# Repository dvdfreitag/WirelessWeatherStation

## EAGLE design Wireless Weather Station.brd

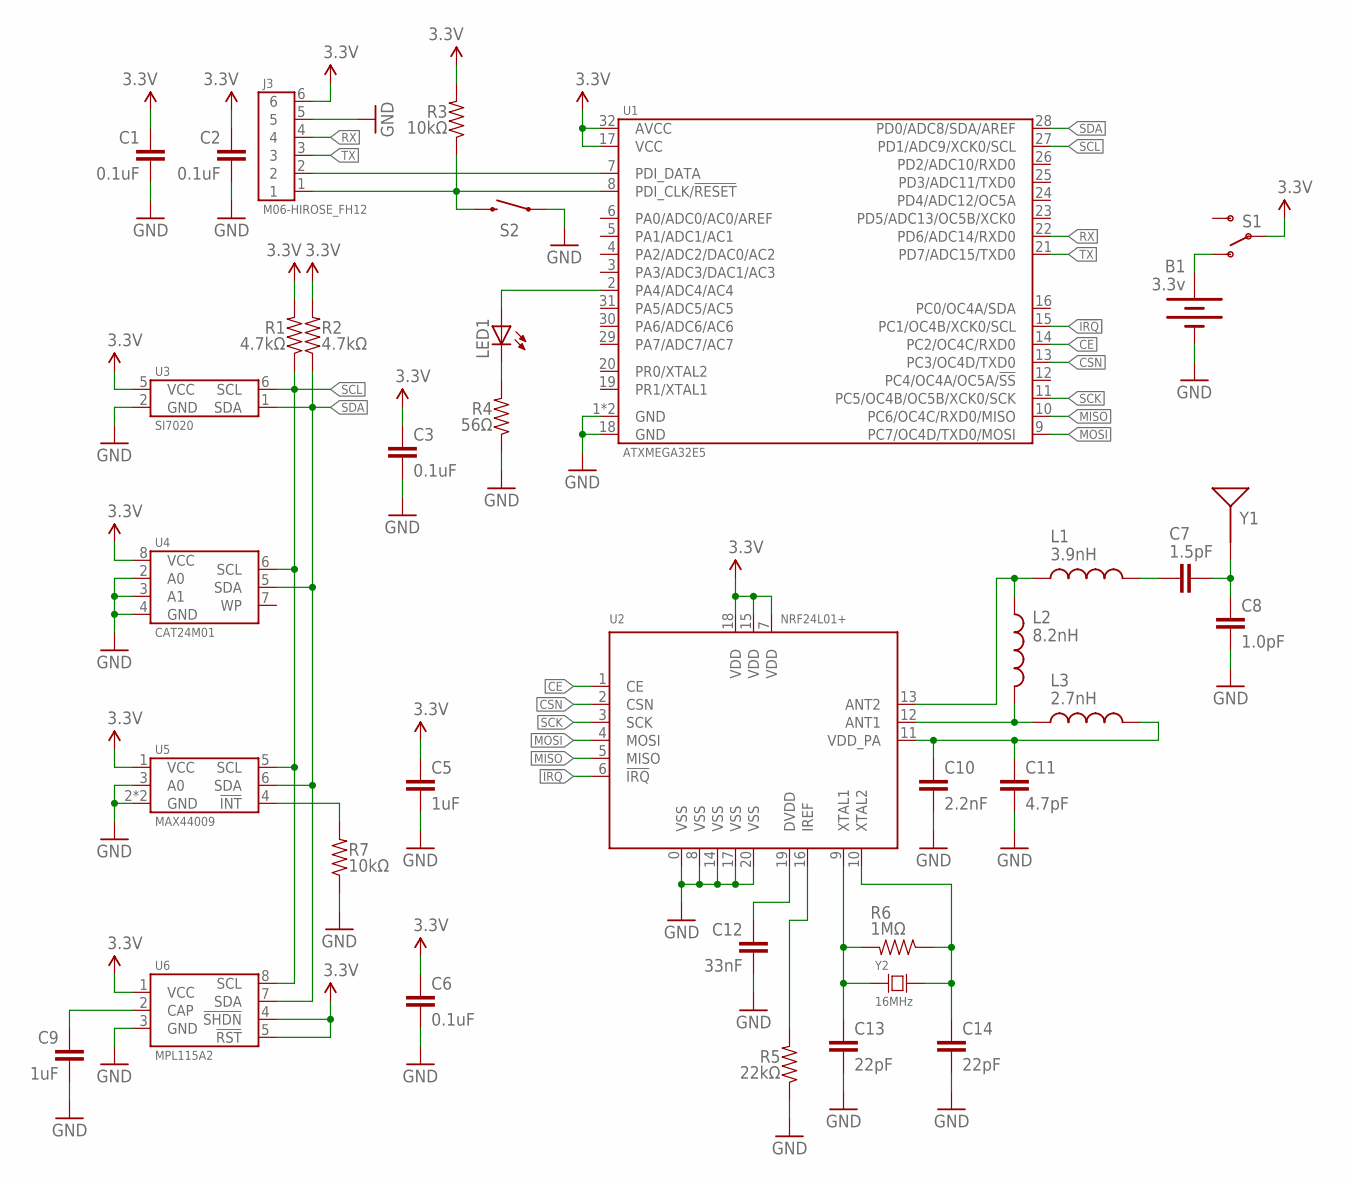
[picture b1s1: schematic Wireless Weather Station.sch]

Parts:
B1: 3.3v; BATTCON_20MM_SEWABLE
C1, C2, C3, C6: 0.1uF; 0402-CAP
C5, C9: 1uF; 0402-CAP
C7: 1.5pF; 0402-CAP
C8: 1.0pF; 0402-CAP
C10: 2.2nF; 0402-CAP
C11: 4.7pF; 0402-CAP
C12: 33nF; 0402-CAP
C13, C14: 22pF; 0402-CAP
J3: M06-HIROSE_FH12; FH12-6S-1SH(55)
L1: 3.9nH; C0402
L2: 8.2nH; C0402
L3: 2.7nH; C0402
LED1: LED0603; LED-0603
R1, R2: 4.7kΩ; 0402-RES
R3, R7: 10kΩ; 0402-RES
R4: 56Ω; 0402-RES
R5: 22kΩ; 0402-RES
R6: 1MΩ; 0402-RES
S1: SWITCH-SPDT-SMD-A; SWITCH-SPST-SMD-A
S2: SWITCH-MOMENTARY-2-SMD-1101NE; TACTILE-SWITCH-1101NE
U1: ATXMEGA32E5; QFN-32
U2: NRF24L01+; QFN-20
U3: SI7020
U4: CAT24M01; SO-8
U5: MAX44009
U6: MPL115A2; MPL115A1
Y1: ANTENNA2SMD5; ANTENNA-CHIP5
Y2: 16MHz; FA-238

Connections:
3.3V: C1.1, C2.1, C3.1, C5.1, C6.1, J3.6, R1.2, R2.2, R3.2, S1.2, U1.17 (VCC), U1.32 (AVCC), U2.7 (VDD), U2.15 (VDD), U2.18 (VDD), U3.5 (VCC), U4.8 (VCC), U5.1 (VCC), U6.1 (VCC), U6.4 (!SHDN), U6.5 (!RST)
!IRQ: U1.15 (PC1/OC4B/XCK0/SCL), U2.6 (!IRQ)
CE: U1.14 (PC2/OC4C/RXD0), U2.1 (CE)
CSN: U1.13 (PC3/OC4D/TXD0), U2.2 (CSN)
GND: B1.2 (-), C1.2, C2.2, C3.2, C5.2, C6.2, C8.2, C9.2, C10.2, C11.2, C12.2, C13.2, C14.2, J3.5, R4.1, R5.1, R7.1, S2.P$1 (1), U1.1 (GND), U1.18 (GND), U1.EP (GND), U2.0 (VSS), U2.8 (VSS), U2.14 (VSS), U2.17 (VSS), U2.20 (VSS), U3.2 (GND), U4.2 (A0), U4.3 (A1), U4.4 (GND), U5.2 (GND), U5.3 (A0), U5.PAD (GND), U6.3 (GND)
MISO: U1.10 (PC6/OC4C/RXD0/MISO), U2.5 (MISO)
MOSI: U1.9 (PC7/OC4D/TXD0/MOSI), U2.4 (MOSI)
unnamed: C7.1, L1.2
unnamed: C9.1, U6.2 (CAP)
unnamed: B1.1 (+), S1.1 (O)
unnamed: J3.1, R3.1, S2.P$2 (2), U1.8 (PDI_CLK/!RESET)
unnamed: LED1.C, R4.2
unnamed: J3.2, U1.7 (PDI_DATA)
unnamed: LED1.A, U1.2 (PA4/ADC4/AC4)
unnamed: C7.2, C8.1, Y1.FEED
unnamed: R5.2, U2.16 (IREF)
unnamed: L1.1, L2.1, U2.13 (ANT2)
unnamed: C10.1, C11.1, L3.2, U2.11 (VDD_PA)
unnamed: L2.2, L3.1, U2.12 (ANT1)
unnamed: C12.1, U2.19 (DVDD)
unnamed: C13.1, R6.2, U2.9 (XTAL1), Y2.1
unnamed: C14.1, R6.1, U2.10 (XTAL2), Y2.3 (2)
unnamed: R7.2, U5.4 (!INT)
RX: J3.4, U1.22 (PD6/ADC14/RXD0)
SCK: U1.11 (PC5/OC4B/OC5B/XCK0/SCK), U2.3 (SCK)
SCL: R1.1, U1.27 (PD1/ADC9/XCK0/SCL), U3.6 (SCL), U4.6 (SCL), U5.5 (SCL), U6.8 (SCL)
SDA: R2.1, U1.28 (PD0/ADC8/SDA/AREF), U3.1 (SDA), U4.5 (SDA), U5.6 (SDA), U6.7 (SDA)
TX: J3.3, U1.21 (PD7/ADC15/TXD0)

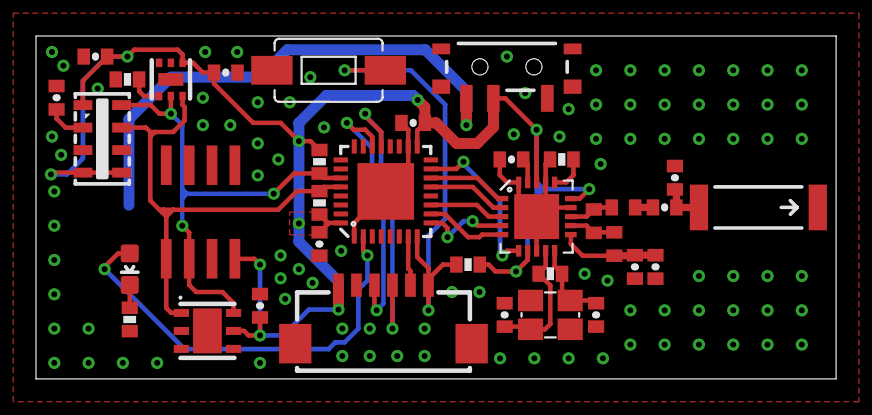
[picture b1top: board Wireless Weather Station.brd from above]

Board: 2 copper layers, 44.5 x 19.1 mm, 36 parts (1 on the bottom side), 28 nets.

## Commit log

2016-08-11 Create LICENSE

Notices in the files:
parts and their libraries:
SparkFun-Passives: Licensing: CC v3.0 Share-Alike You are welcome to use this library for commercial purposes.
SparkFun-LED: Licensing: Creative Commons ShareAlike 4.0 International - https://creativecommons.org/licenses/by-sa/4.0
